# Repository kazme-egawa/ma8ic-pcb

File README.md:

# ma8ic-pcb
PCB design data for ma8ic keyboards

Feel free to use or update pcb design in this repository.

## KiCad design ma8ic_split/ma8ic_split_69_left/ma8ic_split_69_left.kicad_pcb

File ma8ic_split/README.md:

# ma8ic split 69
Split keyboard with 69 keyswitches for a mac user by a mac user.

## left

## left bottom plate

## right

## right bottom plate

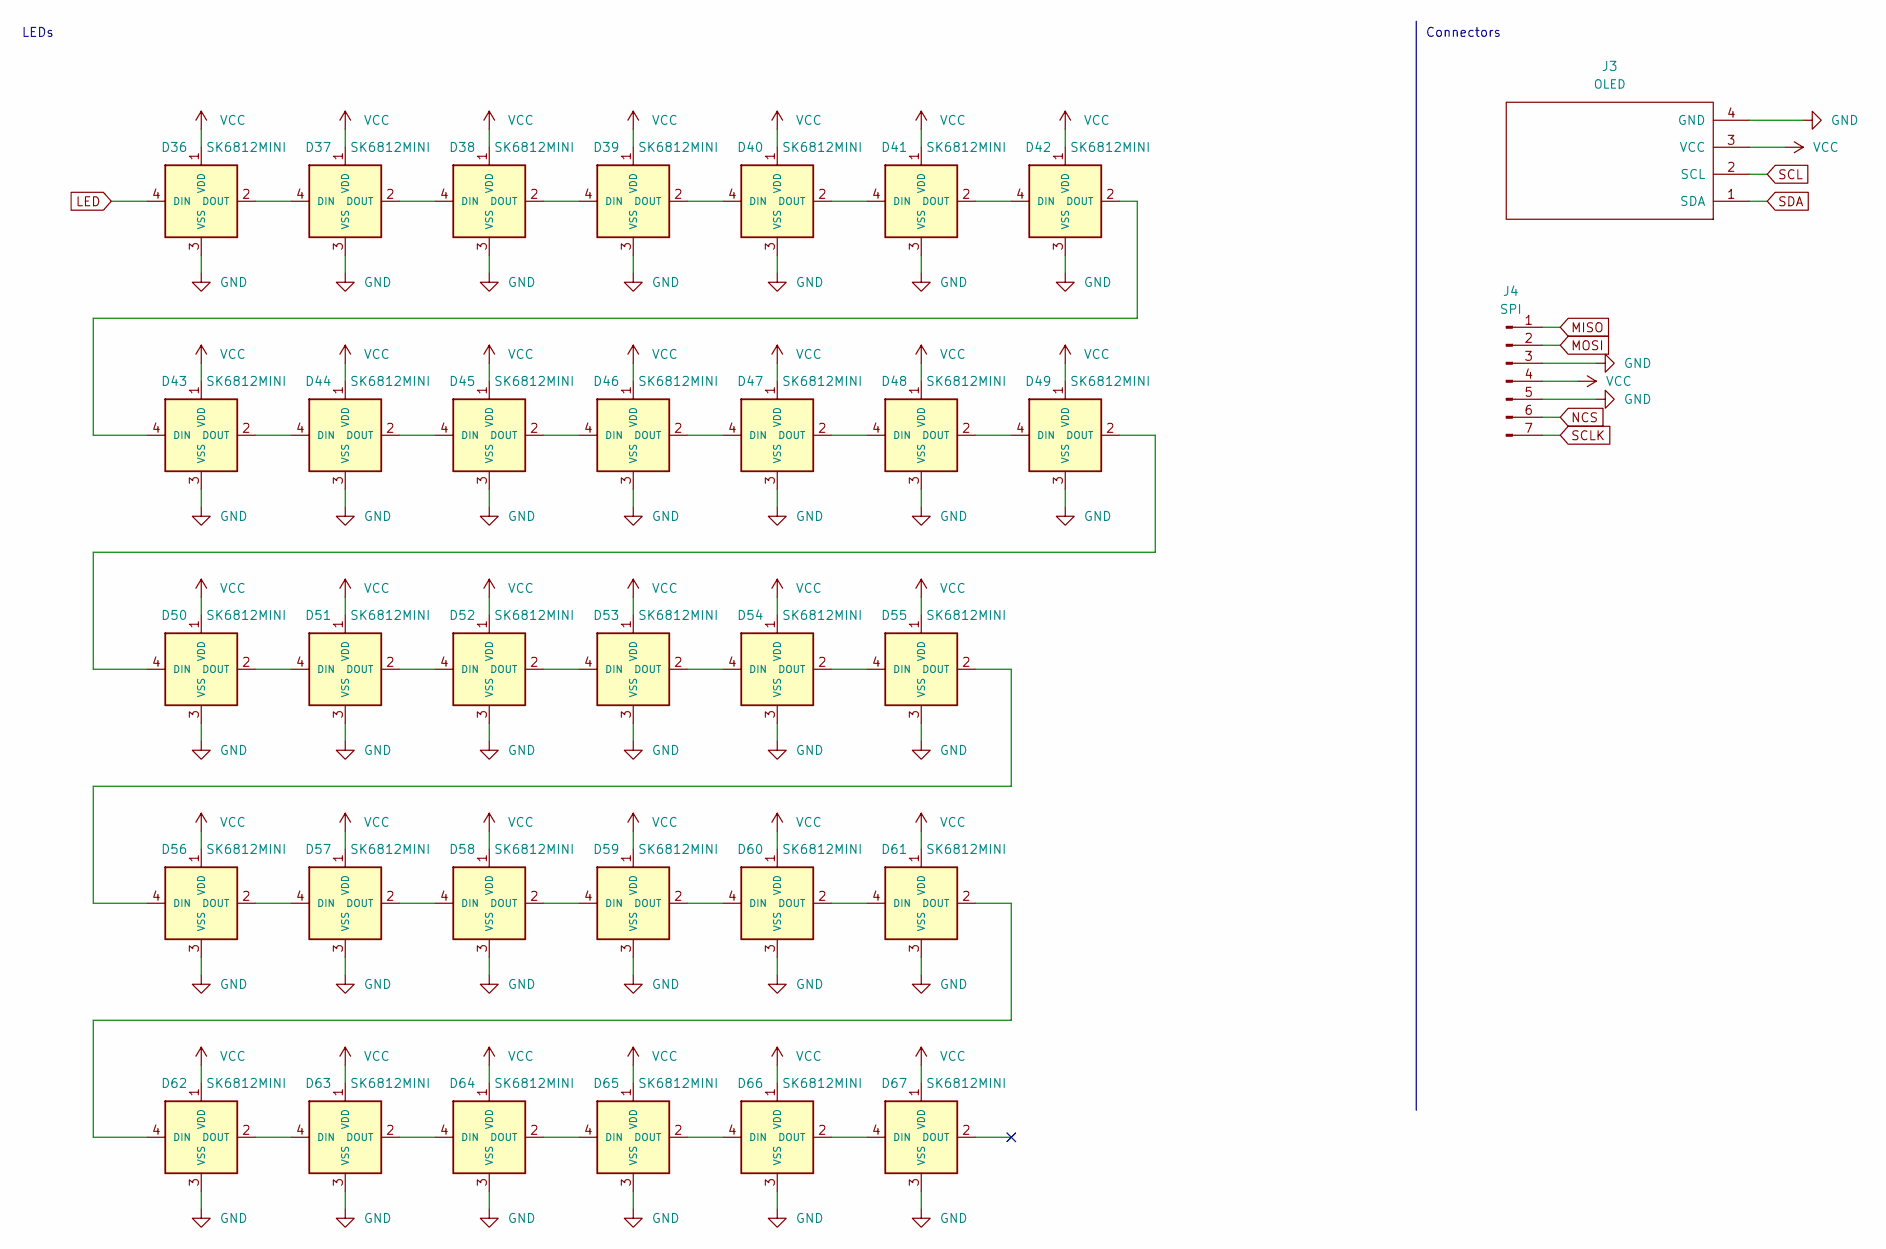
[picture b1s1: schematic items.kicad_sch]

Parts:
D36, D37, D38, D39, D40, D41, D42, D43, D44, D45, D46, D47, D48, D49, D50, D51, D52, D53, D54, D55, D56, D57, D58, D59, D60, D61, D62, D63, D64, D65, D66, D67: SK6812MINI; YS-SK6812MINI-E; LCSC C5149201
J3: OLED; OLED_v2
J4: SPI; PinSocket_1x07_P2.54mm_Vertical

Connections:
GND: D36.3 (VSS), D37.3 (VSS), D38.3 (VSS), D39.3 (VSS), D40.3 (VSS), D41.3 (VSS), D42.3 (VSS), D43.3 (VSS), D44.3 (VSS), D45.3 (VSS), D46.3 (VSS), D47.3 (VSS), D48.3 (VSS), D49.3 (VSS), D50.3 (VSS), D51.3 (VSS), D52.3 (VSS), D53.3 (VSS), D54.3 (VSS), D55.3 (VSS), D56.3 (VSS), D57.3 (VSS), D58.3 (VSS), D59.3 (VSS), D60.3 (VSS), D61.3 (VSS), D62.3 (VSS), D63.3 (VSS), D64.3 (VSS), D65.3 (VSS), D66.3 (VSS), D67.3 (VSS), J3.4 (GND), J4.3, J4.5; also elsewhere on the board
LED: D36.4 (DIN); also elsewhere on the board
MISO: J4.1; also elsewhere on the board
MOSI: J4.2; also elsewhere on the board
NCS: J4.6; also elsewhere on the board
unnamed: D36.2 (DOUT), D37.4 (DIN)
unnamed: D37.2 (DOUT), D38.4 (DIN)
unnamed: D38.2 (DOUT), D39.4 (DIN)
unnamed: D39.2 (DOUT), D40.4 (DIN)
unnamed: D40.2 (DOUT), D41.4 (DIN)
unnamed: D41.2 (DOUT), D42.4 (DIN)
unnamed: D42.2 (DOUT), D43.4 (DIN)
unnamed: D43.2 (DOUT), D44.4 (DIN)
unnamed: D44.2 (DOUT), D45.4 (DIN)
unnamed: D45.2 (DOUT), D46.4 (DIN)
unnamed: D46.2 (DOUT), D47.4 (DIN)
unnamed: D47.2 (DOUT), D48.4 (DIN)
unnamed: D48.2 (DOUT), D49.4 (DIN)
unnamed: D49.2 (DOUT), D50.4 (DIN)
unnamed: D50.2 (DOUT), D51.4 (DIN)
unnamed: D51.2 (DOUT), D52.4 (DIN)
unnamed: D52.2 (DOUT), D53.4 (DIN)
unnamed: D53.2 (DOUT), D54.4 (DIN)
unnamed: D54.2 (DOUT), D55.4 (DIN)
unnamed: D55.2 (DOUT), D56.4 (DIN)
unnamed: D56.2 (DOUT), D57.4 (DIN)
unnamed: D57.2 (DOUT), D58.4 (DIN)
unnamed: D58.2 (DOUT), D59.4 (DIN)
unnamed: D59.2 (DOUT), D60.4 (DIN)
unnamed: D60.2 (DOUT), D61.4 (DIN)
unnamed: D61.2 (DOUT), D62.4 (DIN)
unnamed: D62.2 (DOUT), D63.4 (DIN)
unnamed: D63.2 (DOUT), D64.4 (DIN)
unnamed: D64.2 (DOUT), D65.4 (DIN)
unnamed: D65.2 (DOUT), D66.4 (DIN)
unnamed: D66.2 (DOUT), D67.4 (DIN)
SCL: J3.2 (SCL); also elsewhere on the board
SCLK: J4.7; also elsewhere on the board
SDA: J3.1 (SDA); also elsewhere on the board
VCC: D36.1 (VDD), D37.1 (VDD), D38.1 (VDD), D39.1 (VDD), D40.1 (VDD), D41.1 (VDD), D42.1 (VDD), D43.1 (VDD), D44.1 (VDD), D45.1 (VDD), D46.1 (VDD), D47.1 (VDD), D48.1 (VDD), D49.1 (VDD), D50.1 (VDD), D51.1 (VDD), D52.1 (VDD), D53.1 (VDD), D54.1 (VDD), D55.1 (VDD), D56.1 (VDD), D57.1 (VDD), D58.1 (VDD), D59.1 (VDD), D60.1 (VDD), D61.1 (VDD), D62.1 (VDD), D63.1 (VDD), D64.1 (VDD), D65.1 (VDD), D66.1 (VDD), D67.1 (VDD), J3.3 (VCC), J4.4; also elsewhere on the board

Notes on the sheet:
LEDs
Connectors

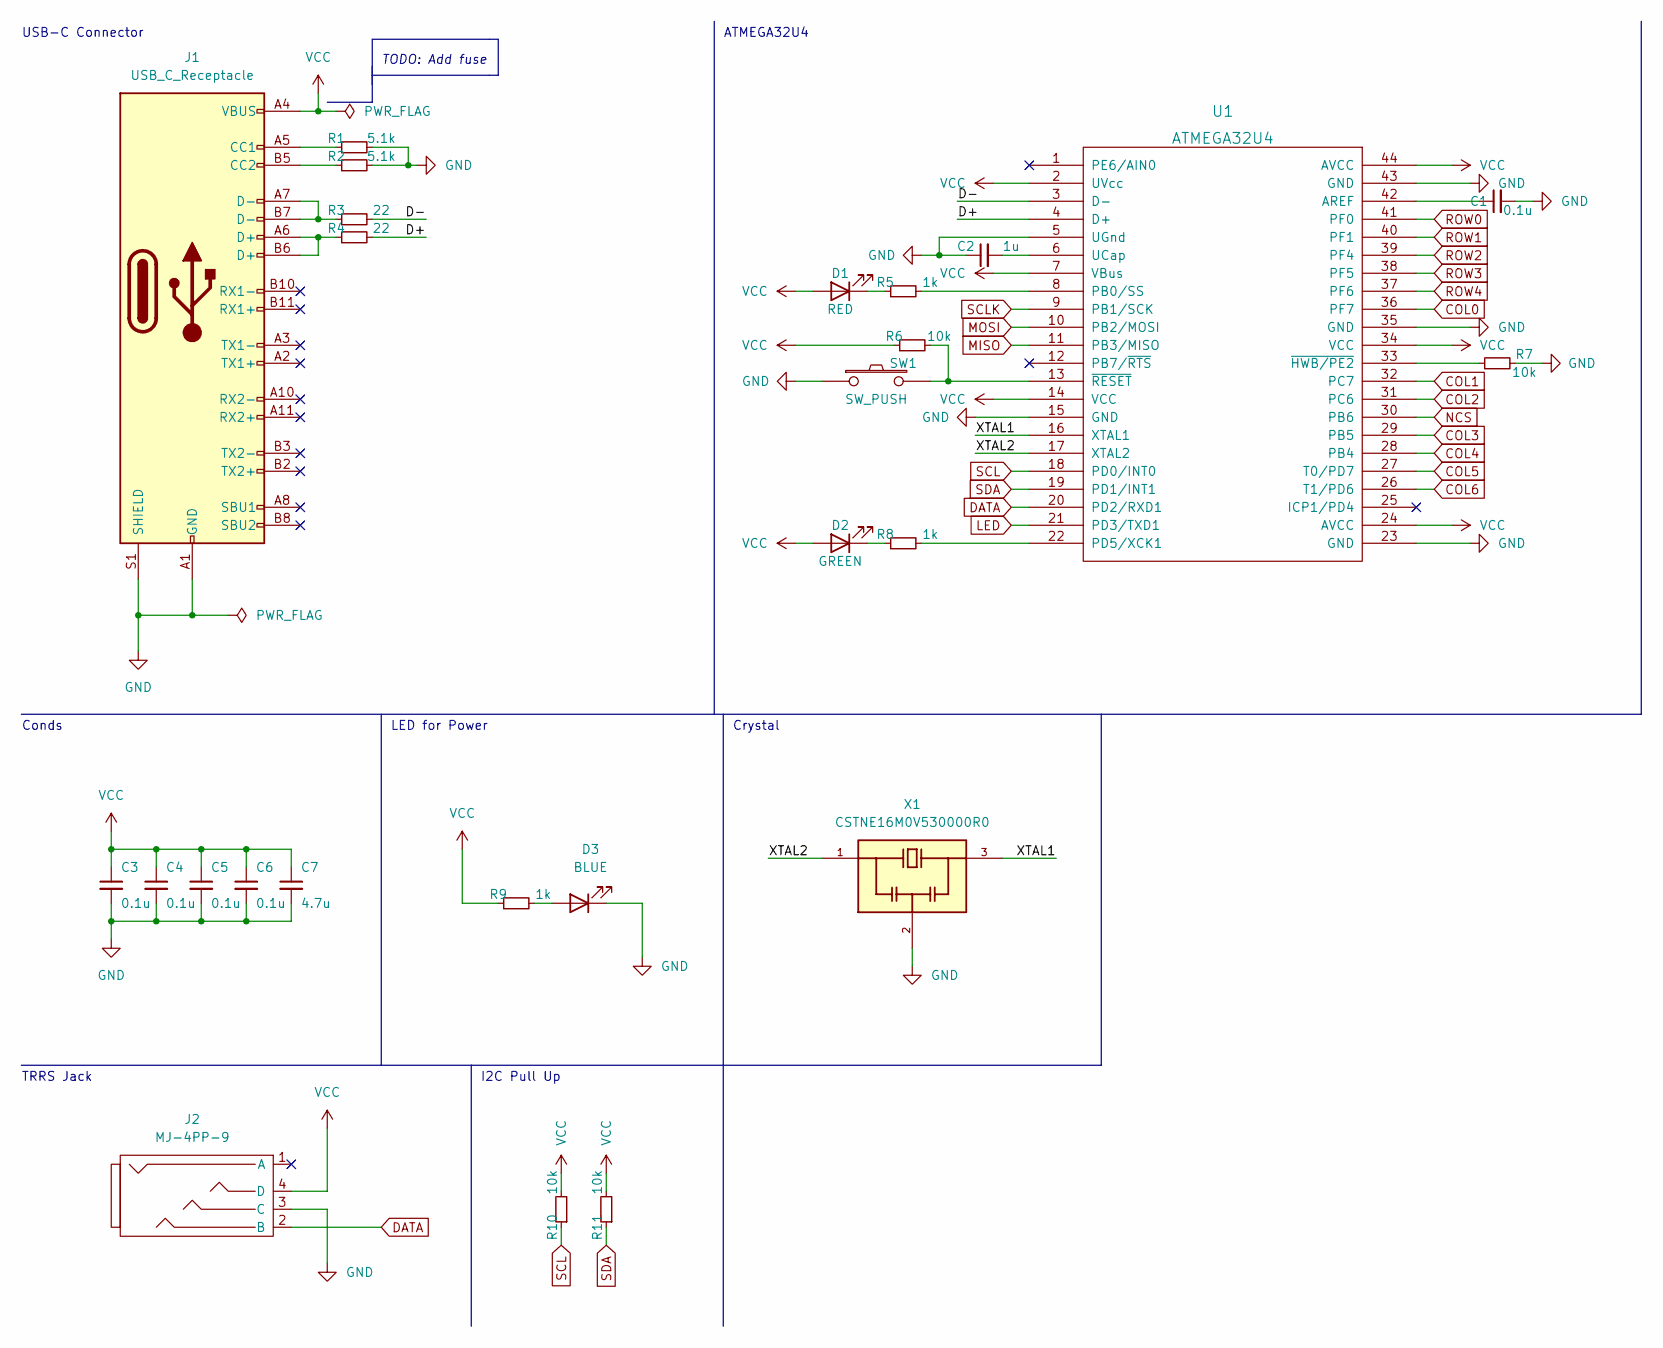
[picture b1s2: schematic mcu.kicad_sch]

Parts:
C1, C3, C4, C5, C6: 0.1u; C_0603_1608Metric; LCSC C14663
C2: 1u; C_0603_1608Metric; LCSC C15849
C7: 4.7u; C_0603_1608Metric; LCSC C19666
D1: RED; LED_0603_1608Metric; LCSC C84263
D2: GREEN; LED_0603_1608Metric; LCSC C84263
D3: BLUE; LED_0603_1608Metric; LCSC C84266
J1: USB_C_Receptacle; HRS_CX70M-24P1; LCSC C778726
J2: MJ-4PP-9; MJ-4PP-9_1side
R1, R2: 5.1k; R_0603_1608Metric; LCSC C23186
R3, R4: 22; R_0603_1608Metric; LCSC C23345
R5, R8, R9: 1k; R_0603_1608Metric; LCSC C21190
R6, R7, R10, R11: 10k; R_0603_1608Metric; LCSC C25804
SW1: SW_PUSH; ResetSW_1side
U1: ATMEGA32U4; QFN-44-1EP_7x7mm_P0.5mm_EP5.2x5.2mm; LCSC C112161
X1: CSTNE16M0V530000R0; OSC_CSTNE16M0V530000R0; PARTREV JGC42-8853B; LCSC C341521

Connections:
/MCU/D+: R4.2, U1.4 (D+)
/MCU/D-: R3.2, U1.3 (D-)
/MCU/XTAL1: U1.16 (XTAL1), X1.3
/MCU/XTAL2: U1.17 (XTAL2), X1.1
COL0: U1.36 (PF7); also elsewhere on the board
COL1: U1.32 (PC7); also elsewhere on the board
COL2: U1.31 (PC6); also elsewhere on the board
COL3: U1.29 (PB5); also elsewhere on the board
COL4: U1.28 (PB4); also elsewhere on the board
COL5: U1.27 (T0/PD7); also elsewhere on the board
DATA: J2.2 (B), U1.20 (PD2/RXD1)
GND: C1.2, C2.1, C3.2, C4.2, C5.2, C6.2, C7.2, D3.1 (K), J1.A1 (GND), J1.A12 (GND), J1.B1 (GND), J1.B12 (GND), J1.S1 (SHIELD), J2.3 (C), R1.2, R2.2, R7.2, SW1.1, U1.5 (UGnd), U1.15 (GND), U1.23 (GND), U1.35 (GND), U1.43 (GND), X1.2; also elsewhere on the board
LED: U1.21 (PD3/TXD1); also elsewhere on the board
MISO: U1.11 (PB3/MISO); also elsewhere on the board
MOSI: U1.10 (PB2/MOSI); also elsewhere on the board
NCS: U1.30 (PB6); also elsewhere on the board
unnamed: C1.1, U1.42 (AREF)
unnamed: C2.2, U1.6 (UCap)
unnamed: D1.1 (K), R5.1
unnamed: D2.1 (K), R8.1
unnamed: D3.2 (A), R9.2
unnamed: J1.A5 (CC1), R1.1
unnamed: J1.A6 (D+), J1.B6 (D+), R4.1
unnamed: J1.A7 (D-), J1.B7 (D-), R3.1
unnamed: J1.B5 (CC2), R2.1
unnamed: R5.2, U1.8 (PB0/SS)
unnamed: R6.2, SW1.2, U1.13 (~RESET)
unnamed: R7.1, U1.33 (~HWB/PE2)
unnamed: R8.2, U1.22 (PD5/XCK1)
ROW0: U1.41 (PF0); also elsewhere on the board
ROW1: U1.40 (PF1); also elsewhere on the board
ROW2: U1.39 (PF4); also elsewhere on the board
ROW3: U1.38 (PF5); also elsewhere on the board
ROW4: U1.37 (PF6); also elsewhere on the board
SCL: R10.1, U1.18 (PD0/INT0); also elsewhere on the board
SCLK: U1.9 (PB1/SCK); also elsewhere on the board
SDA: R11.1, U1.19 (PD1/INT1); also elsewhere on the board
VCC: C3.1, C4.1, C5.1, C6.1, C7.1, D1.2 (A), D2.2 (A), J1.A4 (VBUS), J1.A9 (VBUS), J1.B4 (VBUS), J1.B9 (VBUS), J2.4 (D), R6.1, R9.1, R10.2, R11.2, U1.2 (UVcc), U1.7 (VBus), U1.14 (VCC), U1.24 (AVCC), U1.34 (VCC), U1.44 (AVCC); also elsewhere on the board

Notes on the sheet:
Conds
ATMEGA32U4
TRRS Jack
Crystal
TODO: Add fuse
USB-C Connector
I2C Pull Up
LED for Power

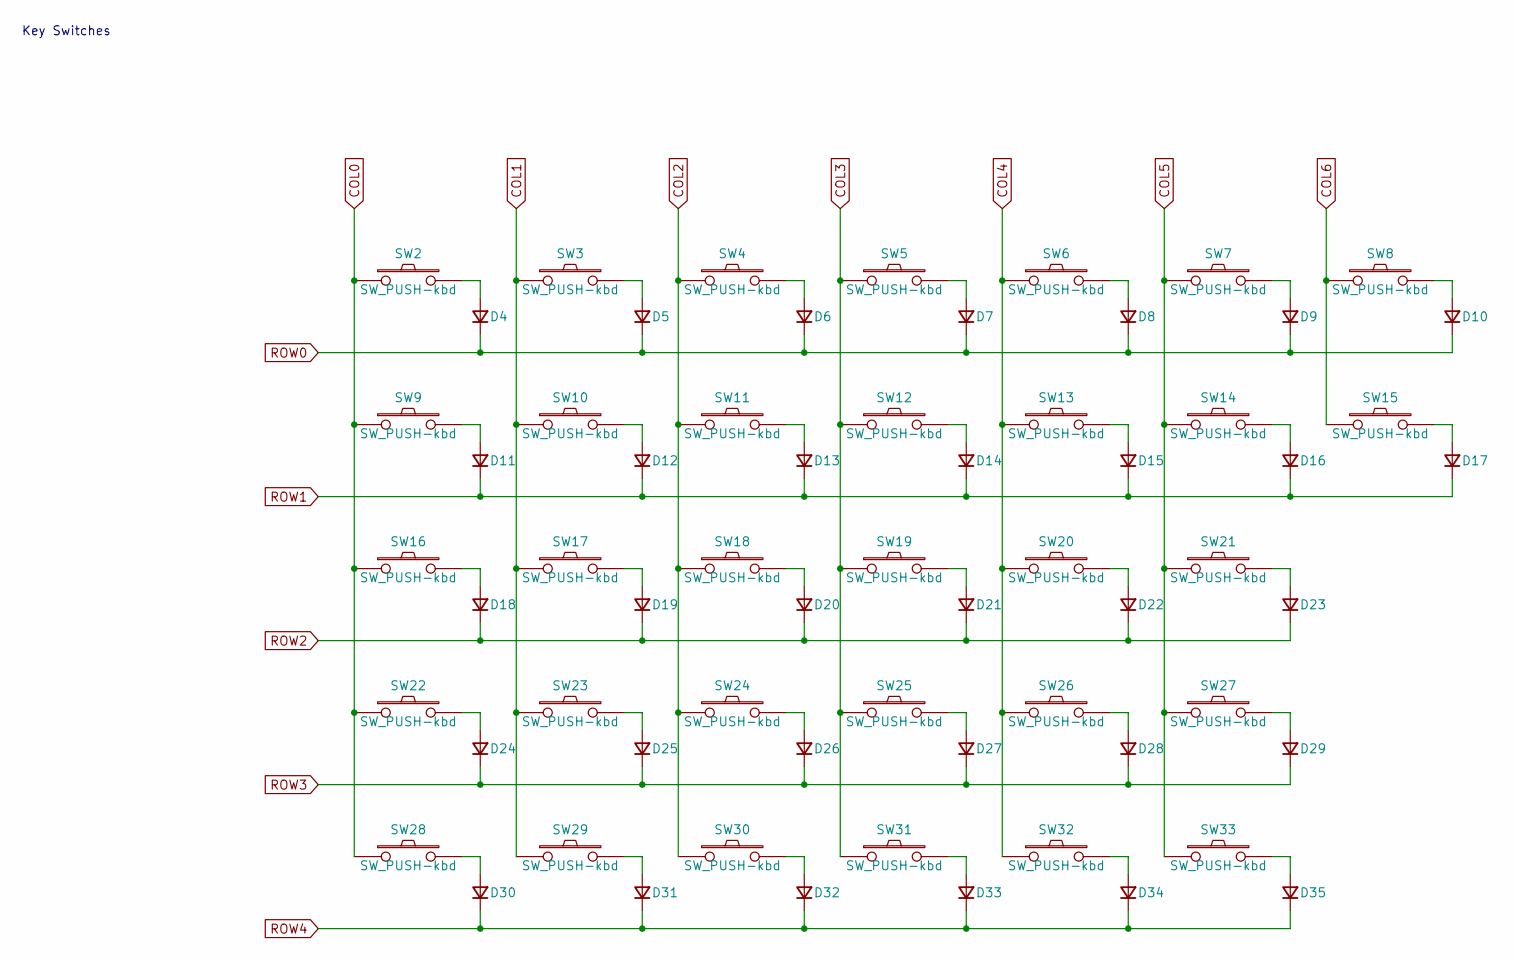
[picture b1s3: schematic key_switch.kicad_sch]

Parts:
D4, D5, D6, D7, D8, D9, D10, D11, D12, D13, D14, D15, D16, D17, D18, D19, D20, D21, D22, D23, D24, D25, D26, D27, D28, D29, D30, D31, D32, D33, D34, D35: D_Small; D3_SMD_v2; LCSC C81598
SW2, SW3, SW4, SW5, SW6, SW7, SW8, SW9, SW10, SW11, SW12, SW13, SW14, SW15, SW16, SW17, SW18, SW19, SW20, SW21, SW22, SW23, SW24, SW25, SW26, SW27, SW28, SW29, SW30, SW31, SW32, SW33: SW_PUSH-kbd; ChocV1_V2_Hotswap; LCSC C5333465

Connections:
COL0: SW2.1, SW9.1, SW16.1, SW22.1, SW28.1; also elsewhere on the board
COL1: SW3.1, SW10.1, SW17.1, SW23.1, SW29.1; also elsewhere on the board
COL2: SW4.1, SW11.1, SW18.1, SW24.1, SW30.1; also elsewhere on the board
COL3: SW5.1, SW12.1, SW19.1, SW25.1, SW31.1; also elsewhere on the board
COL4: SW6.1, SW13.1, SW20.1, SW26.1, SW32.1; also elsewhere on the board
COL5: SW7.1, SW14.1, SW21.1, SW27.1, SW33.1; also elsewhere on the board
unnamed: D4.2 (A), SW2.2
unnamed: D5.2 (A), SW3.2
unnamed: D6.2 (A), SW4.2
unnamed: D7.2 (A), SW5.2
unnamed: D8.2 (A), SW6.2
unnamed: D9.2 (A), SW7.2
unnamed: D11.2 (A), SW9.2
unnamed: D12.2 (A), SW10.2
unnamed: D13.2 (A), SW11.2
unnamed: D14.2 (A), SW12.2
unnamed: D15.2 (A), SW13.2
unnamed: D16.2 (A), SW14.2
unnamed: D17.2 (A), SW15.2
unnamed: D18.2 (A), SW16.2
unnamed: D19.2 (A), SW17.2
unnamed: D20.2 (A), SW18.2
unnamed: D21.2 (A), SW19.2
unnamed: D22.2 (A), SW20.2
unnamed: D23.2 (A), SW21.2
unnamed: D24.2 (A), SW22.2
unnamed: D25.2 (A), SW23.2
unnamed: D26.2 (A), SW24.2
unnamed: D27.2 (A), SW25.2
unnamed: D28.2 (A), SW26.2
unnamed: D29.2 (A), SW27.2
unnamed: D30.2 (A), SW28.2
unnamed: D31.2 (A), SW29.2
unnamed: D32.2 (A), SW30.2
unnamed: D33.2 (A), SW31.2
unnamed: D34.2 (A), SW32.2
unnamed: D35.2 (A), SW33.2
ROW0: D4.1 (K), D5.1 (K), D6.1 (K), D7.1 (K), D8.1 (K), D9.1 (K), D10.1 (K); also elsewhere on the board
ROW1: D11.1 (K), D12.1 (K), D13.1 (K), D14.1 (K), D15.1 (K), D16.1 (K), D17.1 (K); also elsewhere on the board
ROW2: D18.1 (K), D19.1 (K), D20.1 (K), D21.1 (K), D22.1 (K), D23.1 (K); also elsewhere on the board
ROW3: D24.1 (K), D25.1 (K), D26.1 (K), D27.1 (K), D28.1 (K), D29.1 (K); also elsewhere on the board
ROW4: D30.1 (K), D31.1 (K), D32.1 (K), D33.1 (K), D34.1 (K), D35.1 (K); also elsewhere on the board

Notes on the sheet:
Key Switches

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
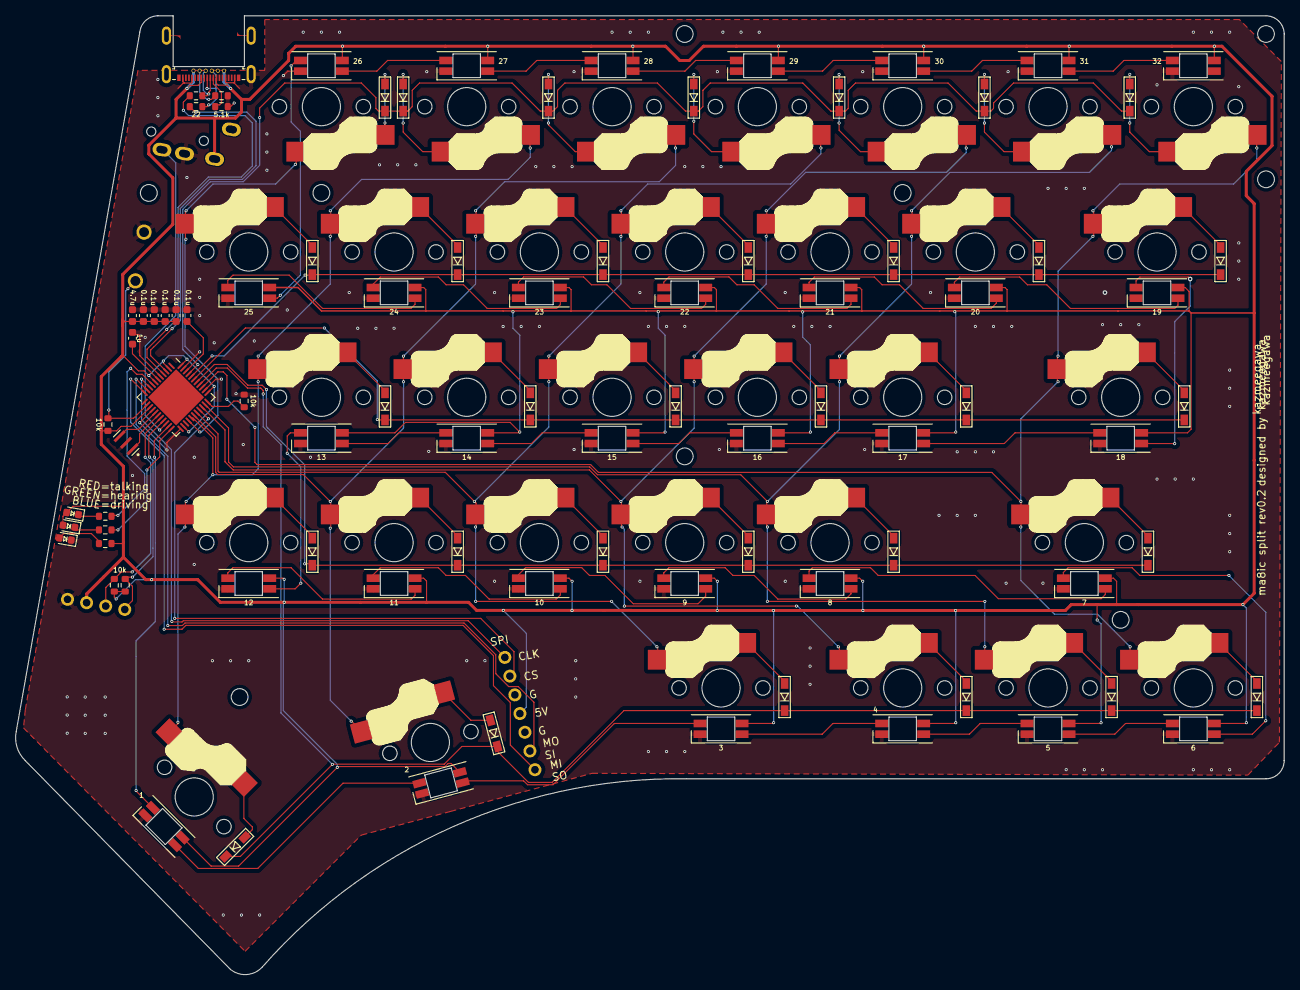
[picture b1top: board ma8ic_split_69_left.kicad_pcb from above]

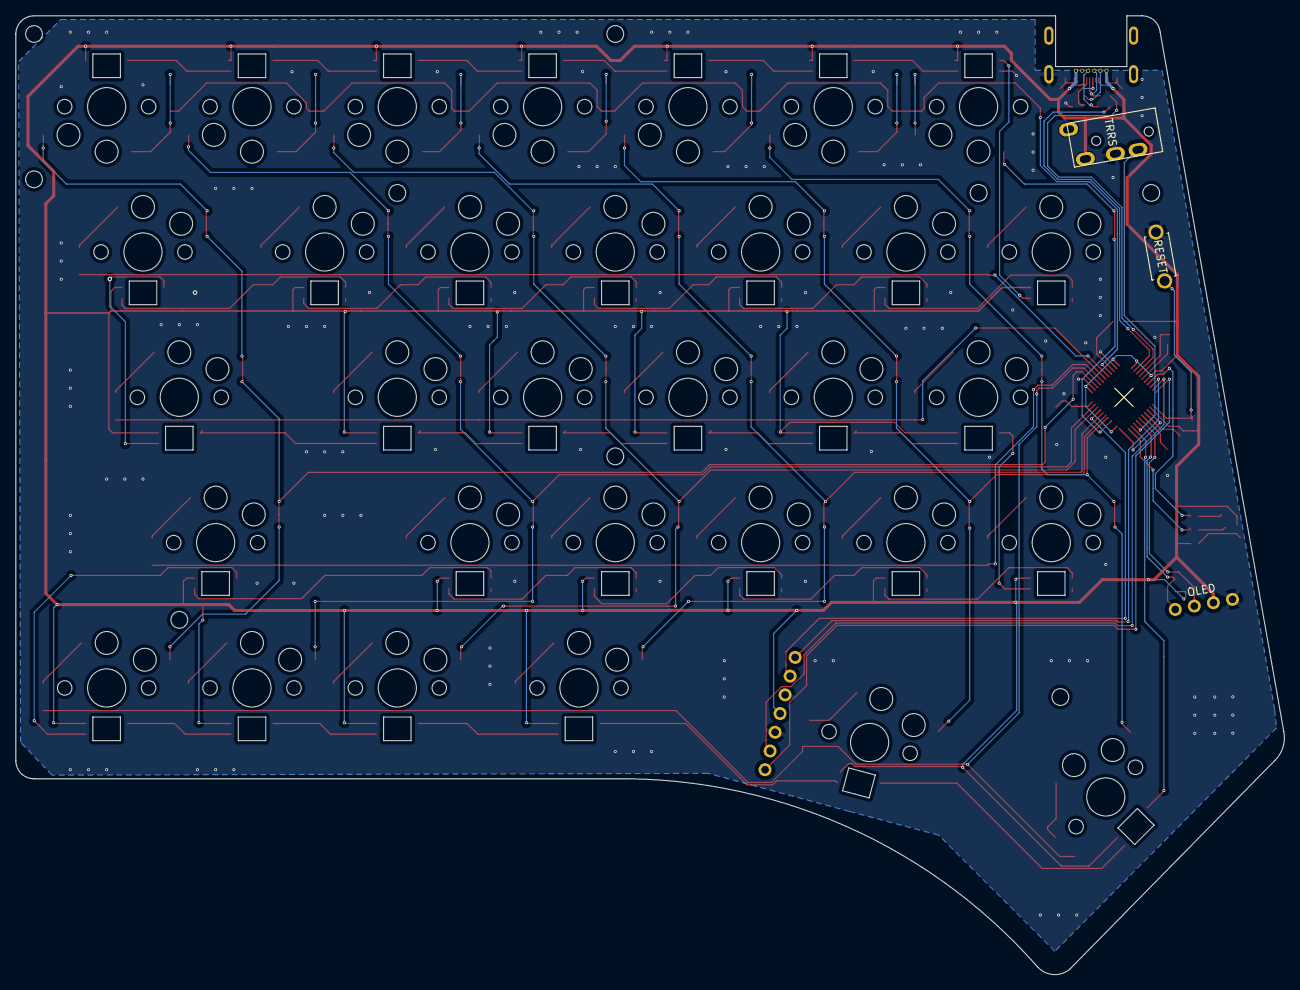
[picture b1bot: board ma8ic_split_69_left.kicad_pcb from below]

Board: 2 copper layers, 166.3 x 125.7 mm, 124 parts (35 on the bottom side), 102 nets.

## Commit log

2023-01-01 init kicad project 69'
2023-01-01 update schematic
2023-01-03 add gbr
2023-01-03 update pos
